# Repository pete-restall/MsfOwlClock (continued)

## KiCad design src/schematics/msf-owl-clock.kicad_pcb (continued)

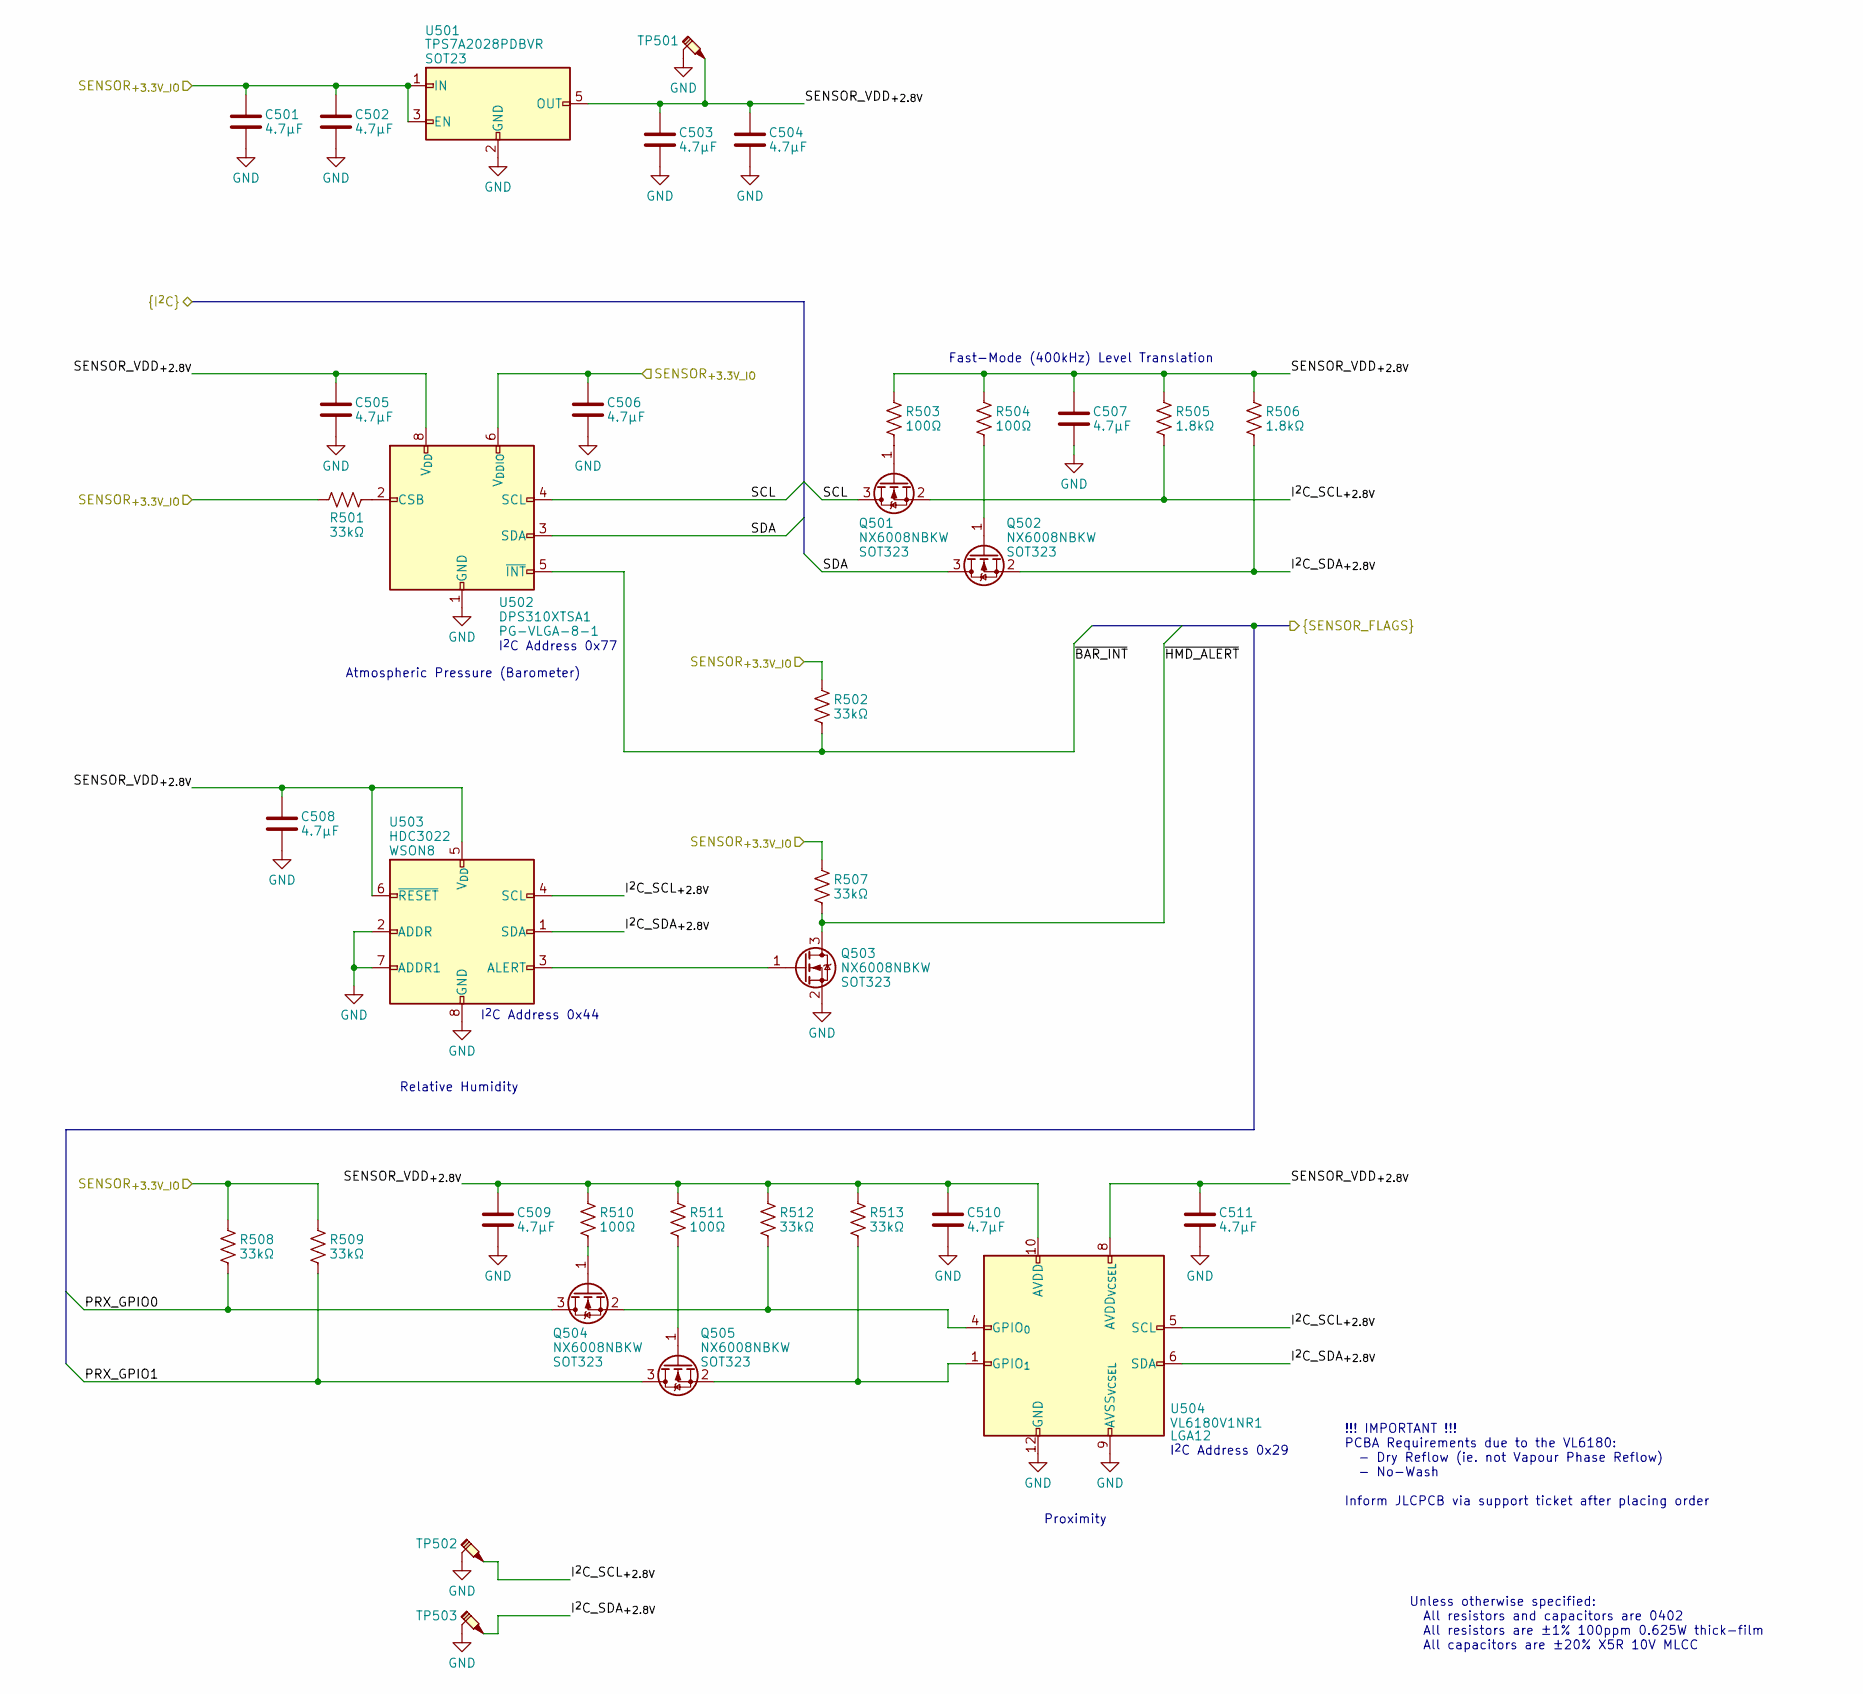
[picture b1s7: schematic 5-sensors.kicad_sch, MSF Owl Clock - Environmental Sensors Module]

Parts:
C501, C502, C503, C504, C505, C506, C507, C508, C509, C510, C511: 4.7μF; unpolarised-nominal-0402-1005; Tolerance ±20%; VoltageRating 10V; ManufacturerPartNumber CL05A475MP5NRNC
Q501, Q502, Q503, Q504, Q505: NX6008NBKW; SOT323; ManufacturerPartNumber NX6008NBKW
R501, R502, R507, R508, R509, R512, R513: 33kΩ; nominal-0402-1005; Tolerance ±1%; ManufacturerPartNumber WR04X3302FTL
R503, R504, R510, R511: 100Ω; nominal-0402-1005; Tolerance ±1%; ManufacturerPartNumber WR04X1000FTL
R505, R506: 1.8kΩ; nominal-0402-1005; Tolerance ±1%; ManufacturerPartNumber RC0402FR-071K8L
TP501, TP502, TP503: testpoint-SP3050A-with-short-gnd
U501: TPS7A2028PDBVR; TPS7A20??PDBVR; ManufacturerPartNumber TPS7A2028PDBVR
U502: DPS310XTSA1; PG-VLGA-8-1-2.0x2.5mm-0.65mm; ManufacturerPartNumber DPS310XTSA1
U503: HDC3022; WSON8-2.5x2.5mm-0.5mm-expad-1.2x1.9mm-thermvias; ManufacturerPartNumber HDC3022DEJR
U504: VL6180V1NR1; OPTICAL-LGA12-2.8x4.8mm-0.75mm; ManufacturerPartNumber VL6180V1NR1-1

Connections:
/1-usb-and-power/SCL: Q501.3 (D), U502.4 (SCL); also elsewhere on the board
/1-usb-and-power/SDA: Q502.3 (D), U502.3 (SDA); also elsewhere on the board
/3-mcu-core/PRX_GPIO0: Q504.3 (D), R508.2; also elsewhere on the board
/3-mcu-core/PRX_GPIO1: Q505.3 (D), R509.2; also elsewhere on the board
/3-mcu-core/~BAR_INT: R502.2, U502.5 (~INT); also elsewhere on the board
/3-mcu-core/~HMD_ALERT: Q503.3 (D), R507.2; also elsewhere on the board
/5-sensors/I^{2}C_SCL_{+2.8V}: Q501.2 (S), R505.2, TP502.1, U503.4 (SCL), U504.5 (SCL)
/5-sensors/I^{2}C_SDA_{+2.8V}: Q502.2 (S), R506.2, TP503.1, U503.1 (SDA), U504.6 (SDA)
/5-sensors/SENSOR_VDD_{+2.8V}: C503.1, C504.1, C505.1, C507.1, C508.1, C509.1, C510.1, C511.1, R503.1, R504.1, R505.1, R506.1, R510.1, R511.1, R512.1, R513.1, TP501.1, U501.5 (OUT), U502.8 (V_{DD}), U503.5 (V_{DD}), U503.6 (~RESET), U504.8 (AVDD_{VCSEL}), U504.10 (AVDD)
/CORE_VDD_{+3.3V}: C501.1, C502.1, C506.1, R501.1, R502.1, R507.1, R508.1, R509.1, U501.1 (IN), U501.3 (EN), U502.6 (V_{DDIO}); also elsewhere on the board
unnamed: Q501.1 (G), R503.2
unnamed: Q502.1 (G), R504.2
unnamed: Q503.1 (G), U503.3 (ALERT)
unnamed: Q504.1 (G), R510.2
unnamed: Q504.2 (S), R512.2, U504.4 (GPIO_{0})
unnamed: Q505.1 (G), R511.2
unnamed: Q505.2 (S), R513.2, U504.1 (GPIO_{1})
unnamed: R501.2, U502.2 (CSB)

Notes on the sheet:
Fast-Mode (400kHz) Level Translation
Unless otherwise specified: All resistors and capacitors are 0402 All resistors are ±1% 100ppm 0.625W thick-film All capacitors are ±20% X5R 10V MLCC
I^{2}C Address 0x77
I^{2}C Address 0x44
!!! IMPORTANT !!! PCBA Requirements due to the VL6180: - Dry Reflow (ie. not Vapour Phase Reflow) - No-Wash Inform JLCPCB via support ticket after placing order
Proximity
I^{2}C Address 0x29
Relative Humidity
Atmospheric Pressure (Barometer)

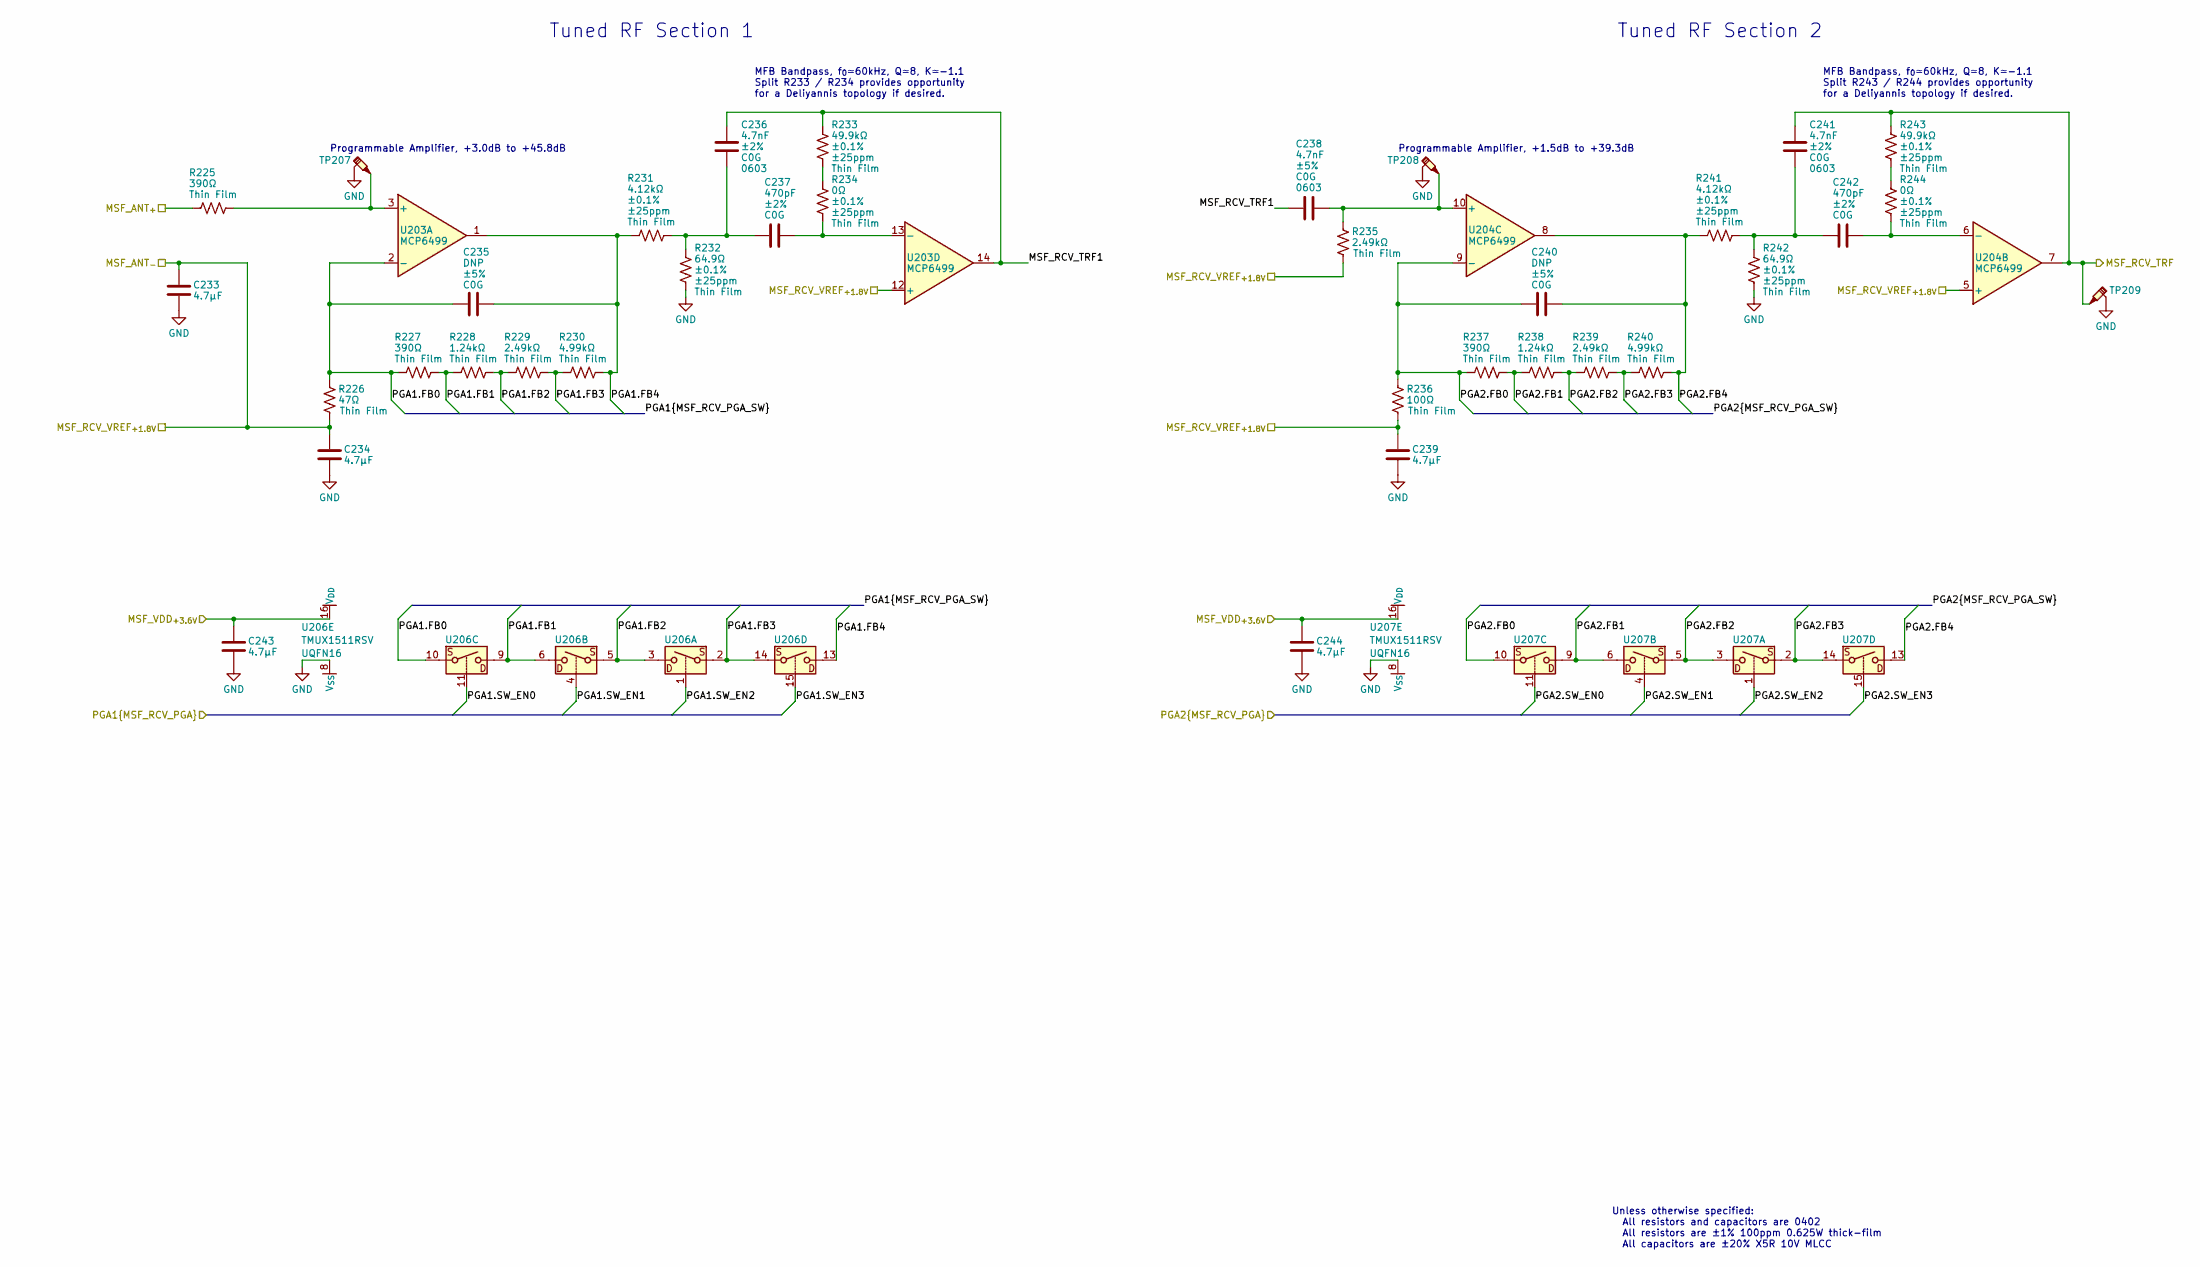
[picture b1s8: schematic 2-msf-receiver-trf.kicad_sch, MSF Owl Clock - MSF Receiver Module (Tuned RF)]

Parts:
C233, C234, C239, C243, C244: 4.7μF; unpolarised-nominal-0402-1005; Tolerance ±20%; VoltageRating 10V; ManufacturerPartNumber CL05A475MP5NRNC
C235, C240: DNP; unpolarised-nominal-0402-1005; Tolerance ±5%; VoltageRating 10V
C236, C241: 4.7nF; unpolarised-nominal-0603-1608; Tolerance ±2%; VoltageRating 10V; ManufacturerPartNumber CC0603FRNPO9BN472
C237, C242: 470pF; unpolarised-nominal-0402-1005; Tolerance ±2%; VoltageRating 10V; ManufacturerPartNumber GCM1555C1H471FA16D
C238: 4.7nF; unpolarised-nominal-0603-1608; Tolerance ±5%; VoltageRating 10V; ManufacturerPartNumber CC0603FRNPO9BN472
R225, R227, R237: 390Ω; nominal-0402-1005; Tolerance ±1%; ManufacturerPartNumber RT0402BRD07390RL
R226: 47Ω; nominal-0402-1005; Tolerance ±1%; ManufacturerPartNumber ERA-2AEB470X
R228, R238: 1.24kΩ; nominal-0402-1005; Tolerance ±1%; ManufacturerPartNumber RT0402BRD071K24L
R229, R235, R239: 2.49kΩ; nominal-0402-1005; Tolerance ±1%; ManufacturerPartNumber RT0402BRD072K49L
R230, R240: 4.99kΩ; nominal-0402-1005; Tolerance ±1%; ManufacturerPartNumber RT0402BRD074K99L
R231, R241: 4.12kΩ; nominal-0402-1005; Tolerance ±0.1%; ManufacturerPartNumber RT0402BRD074K12L
R232, R242: 64.9Ω; nominal-0402-1005; Tolerance ±0.1%; ManufacturerPartNumber RP73PF1E64R9BTD
R233, R243: 49.9kΩ; nominal-0402-1005; Tolerance ±0.1%; ManufacturerPartNumber RT0402BRD0749K9L
R234, R244: 0Ω; nominal-0402-1005; Tolerance ±0.1%; ManufacturerPartNumber RC0402FR-070RL
R236: 100Ω; nominal-0402-1005; Tolerance ±1%; ManufacturerPartNumber RT0402BRD07100RL
TP207, TP208, TP209: testpoint-SP3050A-with-short-gnd
U203, U204: MCP6499; SOIC14-3.9x8.65mm-1.27mm; ManufacturerPartNumber MCP6499T-E-SL
U206, U207: TMUX1511RSV; UQFN16-1.8x2.6mm-0.4mm; ManufacturerPartNumber TMUX1511RSVR

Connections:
/2-msf-receiver/2-msf-receiver-trf/MSF_RCV_TRF: C241.2, R243.1, TP209.1, U204.7; also elsewhere on the board
/2-msf-receiver/2-msf-receiver-trf/MSF_RCV_TRF1: C236.2, C238.2, R233.1, U203.14
/2-msf-receiver/2-msf-receiver-trf/PGA1.FB0: C235.1, R226.1, R227.1, U203.2 (-), U206.10
/2-msf-receiver/2-msf-receiver-trf/PGA1.FB1: R227.2, R228.1, U206.6, U206.9
/2-msf-receiver/2-msf-receiver-trf/PGA1.FB2: R228.2, R229.1, U206.3, U206.5
/2-msf-receiver/2-msf-receiver-trf/PGA1.FB3: R229.2, R230.1, U206.2, U206.14
/2-msf-receiver/2-msf-receiver-trf/PGA1.FB4: C235.2, R230.2, R231.1, U203.1, U206.13
/2-msf-receiver/2-msf-receiver-trf/PGA1.SW_EN0: U206.11; also elsewhere on the board
/2-msf-receiver/2-msf-receiver-trf/PGA1.SW_EN1: U206.4; also elsewhere on the board
/2-msf-receiver/2-msf-receiver-trf/PGA1.SW_EN2: U206.1; also elsewhere on the board
/2-msf-receiver/2-msf-receiver-trf/PGA1.SW_EN3: U206.15; also elsewhere on the board
/2-msf-receiver/2-msf-receiver-trf/PGA2.FB0: C240.1, R236.1, R237.1, U204.9 (-), U207.10
/2-msf-receiver/2-msf-receiver-trf/PGA2.FB1: R237.2, R238.1, U207.6, U207.9
/2-msf-receiver/2-msf-receiver-trf/PGA2.FB2: R238.2, R239.1, U207.3, U207.5
/2-msf-receiver/2-msf-receiver-trf/PGA2.FB3: R239.2, R240.1, U207.2, U207.14
/2-msf-receiver/2-msf-receiver-trf/PGA2.FB4: C240.2, R240.2, R241.1, U204.8, U207.13
/2-msf-receiver/2-msf-receiver-trf/PGA2.SW_EN0: U207.11; also elsewhere on the board
/2-msf-receiver/2-msf-receiver-trf/PGA2.SW_EN1: U207.4; also elsewhere on the board
/2-msf-receiver/2-msf-receiver-trf/PGA2.SW_EN2: U207.1; also elsewhere on the board
/2-msf-receiver/2-msf-receiver-trf/PGA2.SW_EN3: U207.15; also elsewhere on the board
/2-msf-receiver/MSF_ANT_{+}: R225.1; also elsewhere on the board
/2-msf-receiver/MSF_RCV_VREF_{+1.8V}: C233.1, C234.1, C239.1, R226.2, R235.2, R236.2, U203.12 (+), U204.5 (+); also elsewhere on the board
/2-msf-receiver/MSF_VDD_{+3.6V}: C243.1, C244.1, U206.16 (V_{DD}), U207.16 (V_{DD}); also elsewhere on the board
unnamed: C236.1, C237.1, R231.2, R232.1
unnamed: C241.1, C242.1, R241.2, R242.1
unnamed: R233.2, R234.1
unnamed: R243.2, R244.1
unnamed: R225.2, TP207.1, U203.3 (+)
unnamed: C237.2, R234.2, U203.13 (-)
unnamed: C242.2, R244.2, U204.6 (-)
unnamed: C238.1, R235.1, TP208.1, U204.10 (+)

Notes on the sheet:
Programmable Amplifier, +1.5dB to +39.3dB
Tuned RF Section 2
Unless otherwise specified: All resistors and capacitors are 0402 All resistors are ±1% 100ppm 0.625W thick-film All capacitors are ±20% X5R 10V MLCC
Tuned RF Section 1
MFB Bandpass, f_{0}≃60kHz, Q≃8, K≃-1.1 Split R243 / R244 provides opportunity for a Deliyannis topology if desired.
Programmable Amplifier, +3.0dB to +45.8dB
MFB Bandpass, f_{0}≃60kHz, Q≃8, K≃-1.1 Split R233 / R234 provides opportunity for a Deliyannis topology if desired.

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
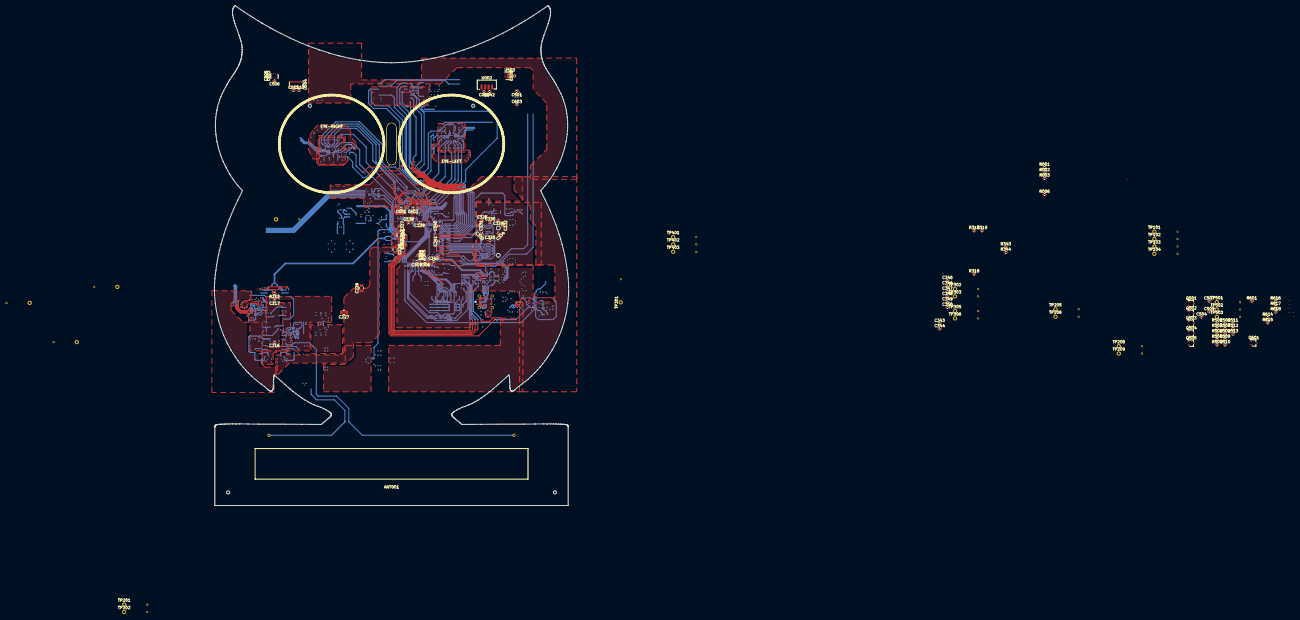
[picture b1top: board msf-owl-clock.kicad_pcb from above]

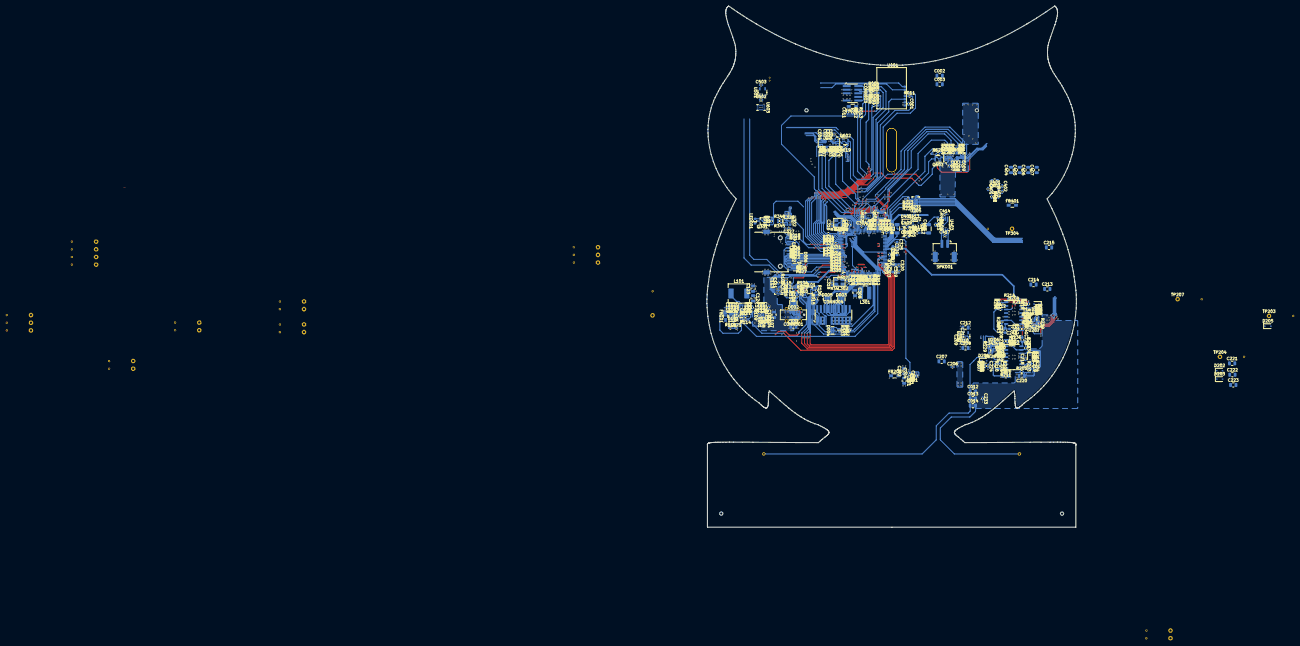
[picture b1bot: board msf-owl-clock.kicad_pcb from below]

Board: 4 copper layers, 130.1 x 183.6 mm, 443 parts (321 on the bottom side), 256 nets.

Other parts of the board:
EYE-LEFT: er-tft1.32-1-eye
EYE-RIGHT: er-tft1.32-1-eye
NT609, NT610: Net Tie; net-tie-2-6mil
TALON-LEFT: talon
TALON-RIGHT: talon

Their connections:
/1-usb-and-power/CORE_VDD_{+5V}: NT609.1 (P1_PWRIN), NT610.1 (P1_PWRIN); also elsewhere on the board

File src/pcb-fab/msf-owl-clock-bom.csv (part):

"Designators","Value","Footprint","Package","Comment","Manufacturer","ManufacturerPartNumber","Quantity"
"C001, C004, C005, C006, C007, C008, C009, C010, C109, C110, C112, C113, C118, C119, C120, C121, C203, C204, C205, C206, C209, C210, C211, C216, C217, C218, C224, C231, C232, C233, C234, C239, C243, C244, C301, C302, C303, C304, C305, C306, C307, C309, C310, C311, C312, C313, C314, C322, C326, C327, C328, C329, C330, C331, C332, C333, C334, C335, C336, C337, C338, C339, C340, C341, C342, C343, C344, C345, C346, C347, C348, C349, C350, C401, C402, C413, C414, C416, C417, C501, C502, C503, C504, C505, C506, C507, C508, C509, C510, C511, C601, C602, C603, C604, C605","4.7μF","unpolarised-nominal-0402-1005","0402","4.7μF±20% 10V X5R","Samsung","CL05A475MP5NRNC","95"
"C002, C116, C117, C123, C124, C201, C202, C207, C208, C212, C213, C214, C220, C221, C222, C226, C227, C308, C403, C404, C405, C406","22μF","unpolarised-nominal-0805-2012","0805","22μF±20% 10V X5R","Samsung","CL21A226MPQNNN","22"
"C230, C238, C409, C410","4.7nF","unpolarised-nominal-0603-1608","0603","4.7nF±5% 10V C0G","Yageo","CC0603FRNPO9BN472","4"
"C011, C107, C321","100nF","unpolarised-nominal-0402-1005","0402","100nF±20% 10V X5R","Samsung","CL05B104KA5NNNC","3"
"C103, C104, C111","100nF","unpolarised-nominal-0402-1005","0402","100nF±20% 25V X5R","Samsung","CL05B104KA5NNNC","3"
"C236, C241, C324","4.7nF","unpolarised-nominal-0603-1608","0603","4.7nF±2% 10V C0G","Yageo","CC0603FRNPO9BN472","3"
"C101, C102","4.7μF","unpolarised-nominal-0805-2012","0805","4.7μF±10% 25V X5R","Samsung","CL21A475KAQNNNE","2"
"C114, C115","470pF","unpolarised-nominal-0402-1005","0402","470pF±10% 25V C0G","Murata","GCM1555C1H471FA16D","2"
"C237, C242","470pF","unpolarised-nominal-0402-1005","0402","470pF±2% 10V C0G","Murata","GCM1555C1H471FA16D","2"
"C315, C316","13pF","unpolarised-nominal-0402-1005","0402","13pF±1% 10V C0G","Murata","GJM1555C1H130FB01D","2"
"C319, C320","16pF","unpolarised-nominal-0402-1005","0402","16pF±1% 10V C0G","Murata","GCM1555C1H160FA16D","2"
"C408, C412","100nF","unpolarised-nominal-1206-3216","1206","100nF±5% 10V C0G","Murata","GRM3195C1H104JA05D","2"
"C106","39pF","unpolarised-nominal-0402-1005","0402","39pF±10% 10V X5R","Yageo","CC0402JRNPO9BN390","1"
"C108","100pF","unpolarised-nominal-0402-1005","0402","100pF±10% 10V X5R","Cal-Chip","GMC04CG101G50NT","1"
"C122","47nF","unpolarised-nominal-0402-1005","0402","47nF±10% 10V X5R","Vishay","VJ0402Y473KXQCW1BC","1"
"C127","10pF","unpolarised-nominal-0402-1005","0402","10pF±5% 10V C0G","Würth Elektronik","885012005007","1"
"C411","22pF","unpolarised-nominal-0402-1005","0402","22pF±5% 10V C0G","Murata","GCM1555C1H220FA16D","1"
"R104, R105, R106, R110, R111, R222, R223, R224, R310, R326, R327, R342, R343, R344, R401, R402, R501, R502, R507, R508, R509, R512, R513, R601, R602, R603, R604, R605, R606, R607, R608, R609, R610, R611, R612, R613, R614, R615, R616, R617, R618","33kΩ","nominal-0402-1005","0402","33kΩ±1% 0.0625W","Walsin","WR04X3302FTL","41"
"R004, R005, R007, R008, R009, R010, R011, R018, R019, R020, R021, R022, R311, R312, R313, R314, R315, R316, R317, R320, R321, R322, R323, R324, R325, R330, R331, R332, R333, R334","43Ω","nominal-0402-1005","0402","43Ω±1% 0.0625W","Yageo","RC0402FR-0743RL","30"
"R002, R003, R006, R012, R301, R302, R303, R304","10kΩ","nominal-0402-1005","0402","10kΩ±1% 0.0625W","Walsin","WR04X1002FTL","8"
"R212, R213, R215, R216, R217, R218","2.49kΩ","nominal-0402-1005","0402","2.49kΩ±0.1% 0.0625W","Yageo","RT0402BRD072K49L","6"
"R318, R319, R340, R341, R505, R506","1.8kΩ","nominal-0402-1005","0402","1.8kΩ±1% 0.0625W","Yageo","RC0402FR-071K8L","6"
"R013, R014, R103, R305, R306","1kΩ","nominal-0402-1005","0402","1kΩ±1% 0.0625W","Walsin","WR04X1001FTL","5"
"R102, R203, R209, R307, R309","0Ω","nominal-0402-1005","0402","0Ω±1% 0.0625W","Yageo","RC0402FR-070RL","5"
"R201, R202, R208, R220, R221","4.99kΩ","nominal-0402-1005","0402","4.99kΩ±0.1% 0.0625W","Yageo","RT0402BRD074K99L","5"
"R335, R336, R337, R338, R339","41.2Ω","nominal-0402-1005","0402","41.2Ω±1% 0.0625W","Yageo","RC0402FR-0741R2L","5"
"R001, R015, R328, R329","330Ω","nominal-0402-1005","0402","330Ω±1% 0.0625W","Walsin","WR04X3300FTL","4"
"R113, R404, R408, R409","19.6kΩ","nominal-0402-1005","0402","19.6kΩ±1% 0.0625W","Walsin","WR04X1962FTL","4"
"R503, R504, R510, R511","100Ω","nominal-0402-1005","0402","100Ω±1% 0.0625W","Walsin","WR04X1000FTL","4"
"R225, R227, R237","390Ω","nominal-0402-1005","0402","390Ω±1% 0.0625W","Yageo","RT0402BRD07390RL","3"
"R229, R235, R239","2.49kΩ","nominal-0402-1005","0402","2.49kΩ±1% 0.0625W","Yageo","RT0402BRD072K49L","3"
"R016, R017","390Ω","nominal-0402-1005","0402","390Ω±1% 0.0625W","Yageo","RC0402FR-07390RL","2"
"R107, R108","2.2Ω","nominal-0402-1005","0402","2.2Ω±1% 0.0625W","Vishay","RMCF0402FT2R20","2"
"R109, R114","3.3kΩ","nominal-0402-1005","0402","3.3kΩ±1% 0.0625W","Walsin","CRCW04022R20FKED","2"
"R205, R211","27Ω","nominal-0402-1005","0402","27Ω±1% 0.0625W","TE Connectivity","CPF0402B27RE1","2"
"R206, R207","4.3kΩ","nominal-0402-1005","0402","4.3kΩ±0.1% 0.0625W","Yageo","RT0402BRD074K3L","2"
"R214, R219","68Ω","nominal-0402-1005","0402","68Ω±0.1% 0.0625W","Yageo","RT0402BRD0768RL","2"
"R228, R238","1.24kΩ","nominal-0402-1005","0402","1.24kΩ±1% 0.0625W","Yageo","RT0402BRD071K24L","2"
"R230, R240","4.99kΩ","nominal-0402-1005","0402","4.99kΩ±1% 0.0625W","Yageo","RT0402BRD074K99L","2"
"R231, R241","4.12kΩ","nominal-0402-1005","0402","4.12kΩ±0.1% 0.0625W","Yageo","RT0402BRD074K12L","2"
"R232, R242","64.9Ω","nominal-0402-1005","0402","64.9Ω±0.1% 0.0625W","TE Connectivity","RP73PF1E64R9BTD","2"
"R233, R243","49.9kΩ","nominal-0402-1005","0402","49.9kΩ±0.1% 0.0625W","Yageo","RT0402BRD0749K9L","2"
"R234, R244","0Ω","nominal-0402-1005","0402","0Ω±0.1% 0.0625W","Yageo","RC0402FR-070RL","2"
"R345, R405","5.1kΩ","nominal-0402-1005","0402","5.1kΩ±1% 0.0625W","Walsin","WR04X5101FTL","2"
"R346, R407","39kΩ","nominal-0402-1005","0402","39kΩ±1% 0.0625W","Yageo","RC0402FR-0739KL","2"
"R619, R620","18Ω","nominal-0402-1005","0402","18Ω±1% 0.0625W","Yageo","RC0402FR-0718RL","2"
"R101","300kΩ","nominal-0402-1005","0402","300kΩ±1% 0.0625W","Yageo","RC0402FR-07300KL","1"
"R112","88.7kΩ","nominal-0402-1005","0402","88.7kΩ±1% 0.0625W","Walsin","WR04X8872FTL","1"
"R226","47Ω","nominal-0402-1005","0402","47Ω±1% 0.0625W","Panasonic","ERA-2AEB470X","1"
"R236","100Ω","nominal-0402-1005","0402","100Ω±1% 0.0625W","Yageo","RT0402BRD07100RL","1"
"R403","68kΩ","nominal-0402-1005","0402","68kΩ±0.1% 0.0625W","KOA Speer","RN73R1ETTP6802B25","1"
"R406","16kΩ","nominal-0402-1005","0402","16kΩ±1% 0.0625W","Yageo","AC0402DR-0716KL","1"
"L101","680nH","07A7","07A7","15.5A_{RMS} / 25A_{SAT}, 5.5mΩ±20% @ DC","Kyocera","LMLP07A7MR68DTAS","1"
"L301","10μH","HPC4018NF","HPC4018NF","1.5A_{RMS} / 1.5A_{SAT}, 150mΩ±20% @ DC","Tai Tech","HPC4018NF-100M","1"
"D101, D201, D202, D203, D204, D205, D206, D401","SD103AWS","SOD323","SOD323",,"Evvo Semi","SD103AWS","8"
"D001, D002, D003, D004, D005, D006, D007","D5V0FS4U10LP","D5V0FS4U10LP","U-DFN2510-10","V_{RWM}=5V V_{CL}=6V V_{BR}=7V C_{d}=0.45pF","Diodes Incorporated","D5V0FS4U10LP","7"
"U601, U602, U603","TMUX1574RSV","UQFN16-1.8x2.6mm-0.4mm","UQFN16",,"Texas Instruments","TMUX1574RSVR","3"
"U203, U204","MCP6499","SOIC14-3.9x8.65mm-1.27mm","SOIC",,"Microchip","MCP6499T-E-SL","2"
"U206, U207","TMUX1511RSV","UQFN16-1.8x2.6mm-0.4mm","UQFN16",,"Texas Instruments","TMUX1511RSVR","2"
"U302, U401","AP22653AW6","SOT26","SOT26",,"Diodes Incorporated","AP22653AW6-7","2"
"U001","BC805M","BC805M","BC805M",,"Fanstel","BC805M","1"
"U002","TSOP75338TT","TSOP7????TT","TSOP753",,"Vishay","TSOP75338TT","1"
"U101","MP5016HGQH","QFN10-1.5x2.0mm-0.5mm","QFN10",,"Monolithic Power Solutions","MP5016HGQH","1"
"U102","BQ24392RSER","UQFN10-1.5x2.0mm-0.5mm","UQFN10",,"Texas Instruments","BQ24392RSER","1"
"U103","FUSB302BMPX","WQFN14-2.5x2.5mm-0.5mm-expad-1.45x1.45mm-thermvias","WQFN14",,"ON Semiconductor","FUSB302BMPX","1"
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
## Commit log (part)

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2023-12-28 Initial commit.
2023-12-28 Added a SPICE simulation for the MSF receiver.
2024-01-01 Started to put the schematics together, mainly around defining and joining the logical blocks, along with the PIC32 pin and peripheral mapping. Lots of notes and some new datasheets / specifications.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
2024-01-06 Added a simulation to verify I2C level shifting.
2024-01-09 Elaboration of the top-level schematicd.
2024-01-19 Fixed some typos in simulation workspace names.
2024-01-21 Further elaboration of the design and schematics, mainly power supply calculations.
2024-01-28 Further elaboration of the USB / Power schematic.
2024-02-21 Started to explore active filtering rather than using crystals for the MSF front-end.
2024-02-21 Started to add some calculations around the MSF front-end but realised the specs are probably too restrictive / ambitious for a simple design. The outcome of the active filtering simulations may be m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
2024-02-22 Tidied up the MSF front-end simulation. Next step - Monte Carlo...
2024-02-24 Added a TODO as a reminder not to forget about discharging the reference rails on power-down.
2024-02-28 Added SVGs of the Monte-Carlo runs for minimum and maximum gains, zoomed into the main portion of interest.
2024-03-04 More logical organisation of the infrared sensor datasheet.
2024-03-11 Added a simple simulation to verify the voltage references and their discharges behave when the +3.6V rail is cut.
2024-03-19 Investigated the effect of some bypass networks on the op-amp outputs (PSRR).
2024-03-20 Started to elaborate the audio output circuitry.
2024-03-23 Finished drawing up the audio output schematic. The speaker selection is still to do.
2024-03-23 Corrected the shutdown current for the TPS7A2040.
2024-03-23 Started to draw up the sensor schematics.
2024-03-25 Drew the schematic for the sensors.
2024-03-26 Started to draw the TFT module's schematic.
2024-03-30 Added the infrared receiver. Various tidy-ups.
2024-04-04 Further elaboration of the circuitry surrounding the microcontroller. Plus a few typos / tidy-ups.
2024-04-16 Added the IBIS models as generated by MicroCap. These will *not* work with ngspice, at least not without modification (the PWL TRIGGER statements are the obvious incompatabilities).
2024-04-18 Added footprints for the ARM debug connectors. Added a datasheet for the speaker connector (Molex 502443-0270).
2024-04-18 Moved the TFT connector datasheet.
2024-04-19 Added the SD Card connector's (MSD-11-A) footprint.
2024-04-20 Added part numbers for the capacitors.
2024-04-20 Started to clean up the ERC flags.
2024-04-21 Some footprint / net bugfixes identified whilst generating the initial PCB.
2024-04-23 [WIP] Rearranging the SD Card and TVS arrangement.
2024-04-23 Simplified the owl PCB outline, made it more symmetrical, and closed the shape correctly so that it acts as a proper board edge.
2024-04-23 Added tooling holes for JLCPCB's PCBA.
2024-04-24 Finalised the location and dimensions of the eyes and their connectors; based on bench measurements.
2024-04-24 PCB routing.
2024-05-03 PCB routing - trying to find the best placement in relation to the radio, regulators and speaker driver.
2024-05-09 Updated to allow up to 1.44W for the SD card, which is actually what UHS-I specifications are measured at; 0.72W is the limit for the default speed mode / driver strength.
2024-06-09 PCB routing. Fixed most of the DRC violations.
2024-06-09 Started to experiment with beaks.
2024-06-11 Finished tweaking. Ready for review and generation of manufacturing files.
2024-06-12 Generated the gerbers, drill files and gerbv project. Needs checking.
2024-06-22 Added the ARM v7 M reference.
2024-06-23 Random vscode reformatting.
2024-06-25 Various hackery and tinkering to poke the picolibc internals, verify hooks, the linker scripts and debugging. Committed as a checkpoint so this junk can be peeled back to enable more meaningful work.
2024-06-27 Added meson as the build system and it now produces the same result as the build.sh script. Test framework next.
2024-06-28 Added specialised Linker{App,Kernel}{Init,Fini}Array classes for encapsulating the STM32L432KC's linker externs.
2024-06-28 Added encapsulation for the STM32L432KC's SRAM-based BSS sections.
2024-06-29 Added encapsulation for the STM32L432KC's SRAM-based (retainable 16KiB) BSS sections.
2024-06-29 Added encapsulation for the STM32L432KC's SRAM-based (retainable 16KiB) data sections.
2024-07-03 Added ChainedInitialisation, which will call a sequence of (unrolled) initialisers (IInitialisable). The memory map will be the first use of this, since the initialisation of the various BSS and data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
2024-07-06 A couple of tests to verify there are no side-effects with zero-length memory sections.
2024-07-06 Added the generic LinkerInitArraySection and removed / tidied up the MCU-specific cruft.
2024-07-07 Added LinkerFiniArraySection.
2024-07-08 Various tweaks to get the application running on hardware again, now that we have proper mechanisms to initialise BSS and data memory, as well as being able to fire off the handlers in the .init and 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
2024-07-13 Reverted the attempt at using C++ modules. The toolchain just isn't ready.
2024-07-16 Mapped some more Arm Cortex M4 register banks.
2024-07-20 Added an IntegerSequence to complement the OffsetIntegerSequence, giving a concept of IHaveValuesOf<T>.
2024-07-20 Changed typedefs into usings and other small tweaks.
2024-07-21 Changed toVector() to asVector() for more consistent naming.
2024-07-21 Added a rudimentary BitfieldTraits which should facilitate (contiguous) bitfield access for registers.
2024-07-25 Started to add crt0 support for the PIC32CX1025SG41100 now that the board has arrived.
2024-07-27 Hacked around with some port pins to verify that the power supplies turn on and ramp correctly. The ramps aren't bad. The USB VBUS droop is probably out of spec when turning on the radio and audio re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
2024-07-27 Changed the directory structure slightly to allow multiple apps, eg. one for hacking / debugging / board exploration, one for the actual implementation.
2024-07-28 Added a simple example of what I would like the tasks and kernel API to look like. This is now something that can be worked towards in a top-down manner.
2024-08-02 Added the TaskLifecycle tests to the build, as well as rejigged the layout of the 'app' directory a little (now 'apps').
2024-08-03 Better randomisation by proper seeding of the RNG - https://codereview.stackexchange.com/questions/109260/seed-stdmt19937-from-stdrandom-device
2024-08-03 Added some compiler hints to the DefaultIdleTask to make for a slightly more efficient implementation.
2024-08-10 Added TasksFrom<TConfig> to accumulate the Tasks that are declared in the kernel / app configurations.
2024-08-12 Some basic tidy-ups.
2024-08-12 Changed pushFront<X>(std::integer_sequence) to consteval.
2024-08-14 Created BubbleSorted<T, Ints...> to allow compile-time sorting of integer sequences.
2024-08-18 Added TaskStacksFrom<TConfig> which will be used to accumulate stacks into linker sections.
2024-08-20 Started splitting out / adding dedicated tests for the functionality currently exercised via TaskStacksFrom. WIP; various TODOs to indicate direction for when I next have time to pick this up.
2024-08-21 Tightened the IHaveConfigForOverlaidTasks constraints to ensure there is always at least one task in an overlay.
2024-10-04 Added xaljox's 'fixpath' (https://github.com/xaljox/fixpath) to fix the annoying vscode problem-matcher limitations that prevent navigation to source files with errors, which is due to the generated 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
2024-10-05 Added rudimentary problem-matchers to highlight mettle test runner failures in the vscode 'Problems' window.
2024-10-05 Exposed the 'TResource' template parameter as a 'ResourceType' member typedef.
2024-10-10 Underscored the utility classes - these will be private once module support is mature enough to switch to.
2024-10-18 Removed TODOs they might be premature optimisations - will wait and see what the rest of the implementation requires.
2024-10-20 Started to think about bootstrapping the first task, which makes sense as kernel initialisation after the static CRT initialisers have been run. Came to the realisation that the kernel / crt0 librari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
2024-10-22 Amended iHaveConfigForTasks to allow arrays as well as tuples.
2024-10-22 Missed build file amendment from previous commit.
2024-11-03 Some thoughts on syscalls, along with a primitive mechanism for leveraging the 'svc' opcode on the ARM Cortex M4.
2024-11-07 Added a workaround to enable constructor injection, necessary because C++ has no reflection and obtaining the address (and therefore signature) of a constructor is not allowed.
2024-11-09 Corrected some typos.
2024-11-10 Added missing template argument that wasn't being deduced.
2024-11-14 A simple utility for converting tuple-likes to an equivalent std::tuple<> for easier specialisations.
2024-11-15 Added Unique, used for removing duplicate element types from tuple-likes (std::tuple, std::array and std::pair). Initially required as part of API discovery from the Config tree; we only need to see 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
2024-11-17 Added parsing of the non-simple (ie. 'Configured') Tasks from Overlay Configs.
2024-11-26 Added the various DriverProvidedIsrConfigsFrom<TConfigs...> implementations, used to extract ISR details from Kernel Configs.
2024-11-29 Added IsrApis<TApis...> and enhanced the IIsr concept to include both INakedIsr and IPerCoreIsr, the latter being able to require APIs.
2024-12-05 Renamed DriverToDriverApis to DriverTaskApis and split out IAppTask and IDriverTask to decouple things a little.
2024-12-05 Cleaned up some TODOs by fixing some dependency arrow directions.
2024-12-07 Tidied up some ISR concerns, mainly for ARM / AAPCS. Verified the assembly generated under several scenarios - both correct and faster. I do have concerns around relying on 'register ... asm(...)' th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
2024-12-07 Added an implementation for the PortableSyscallIsr, which is basically an analogue of the NakedToPerCoreIsrAdapter but with arguments. This is a WIP commit since it only builds for tests due to there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
2024-12-14 Added some more Syscall boilerplate, such as the SyscallApis container and some factories to create the ISR. Stubbed out some things, such as the DefaultSyscallHandlerFactory, to get the project comp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
2024-12-15 Added an implementation for DefaultSyscallHandlerFactory, which entailed splitting out an IHaveRequiredApis concept, which in turn created some opportunities for some minor refactoring.
    Added some TODOs as reminders of future improvements to the factories / configs.
2024-12-15 Mnor tidy-up; hiding un-necessary detail from the public interface.
2024-12-30 There are difficulties with the *Apis containers around construction, testing and test doubles. Conceptually the explicit *Apis containers are only required to facilitate (easier) dependency injectio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
    C++ does not (yet) have reflection, and without the ability to take the address of a constructor to determine its arguments, it seems dependency injection without knowing types up-front is not possib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
    This commit is the first part of a proper DI implementation for the kernel, tailored for static allocation and resource-constrained architectures. The ConstructorParameters class encapsulate
2025-01-03 WIP - started to add an implementation for the DI container. Very basic Register / Resolve functionality at present, with glaring deficiencies and lots more work required to make it usable. This comm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
2025-01-12 Added support for (data) pointers of various CV qualification.
2025-02-02 Added an image of the board with the antenna and TFT displays mounted.
2025-03-11 Trivial casing fix.
2025-03-12 Extracted LambdaFactoryTraits into its own header.
2025-03-12 Added basic pointer resolution using the default factory.
